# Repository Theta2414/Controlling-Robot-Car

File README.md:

# Controlling Robot Car

A wireless robot car control system implemented using STM32. The project uses an STM32-based transmitter and receiver architecture to control the movement of a robot car remotely. Motion commands are generated from user input and transmitted wirelessly to the robot, where the received commands are processed to control the motors.

The project focuses on embedded system development, wireless communication, sensor interfacing, PWM-based motor control, and real-time control using the STM32 microcontroller.

## 1. Project Overview

This project implements a wireless control system for a robot car using STM32 microcontrollers.

The system is divided into two main units:

- **Transmitter (Tx):** Reads user input and generates movement commands.
- **Receiver (Rx):** Receives the commands wirelessly and controls the robot car motors.

The transmitter and receiver communicate in real time, allowing the user to control the robot car's movement remotely.

The system is designed to support basic vehicle movements such as:

- Forward
- Backward
- Turn left
- Turn right
- Stop

PWM signals are used to control the motor speed, while the motor driver handles the required motor direction and power control.

## 2. Learning Objectives

- Practice embedded system development using STM32.
- Understand wireless communication between two embedded systems.
- Interface sensors and input devices with STM32.
- Understand PWM generation and motor speed control.
- Implement real-time control logic on a microcontroller.
- Apply UART/I2C/GPIO/TIMER peripherals where required by the system.
- Understand the separation between transmitter-side and receiver-side firmware.
- Improve debugging, hardware integration, and system-level development skills.
- Gain practical experience in developing a complete embedded system from input acquisition to actuator control.

## 3. System Architecture

The system consists of two main parts: a transmitter unit and a receiver unit.

### 3.1. Transmitter Unit

The transmitter is responsible for obtaining the user's control input and converting it into movement commands.

The general processing flow is:

```text
User Input / Motion Sensor
          ↓
    STM32 Transmitter
          ↓
   Control Processing
          ↓
  Wireless Transmission
```

The transmitter continuously reads the input data, processes the corresponding control information, and sends the resulting command to the receiver.

### 3.2. Receiver Unit

The receiver is installed on the robot car.

It receives the wireless control commands and converts them into motor control signals.

The general processing flow is:

```text
 Wireless Receiver
        ↓
  STM32 Receiver
        ↓
 Command Processing
        ↓
Direction + PWM Generation
        ↓
   Motor Driver
        ↓
    DC Motors
```

This architecture separates user interaction from the motor-control system and allows the robot to be controlled remotely.

## 4. Hardware Overview

The main hardware components used in the project include:

| Component                     | Purpose                    |
| ----------------------------- | -------------------------- |
| STM32F103C8T6                 | Main microcontroller       |
| MPU6050                       | Motion/tilt sensing        |
| Wireless communication module | Transmits control commands |
| Motor driver                  | Drives the DC motors       |
| DC motors                     | Provides robot movement    |
| Robot car chassis             | Mechanical platform        |
| Battery / Power supply        | Provides system power      |
| ST-Link                       | Programming and debugging  |

The STM32F103C8T6 is used as the main processing unit for both the transmitter and receiver sides.

The MPU6050 provides accelerometer and gyroscope measurements that can be processed to estimate the orientation of the transmitter.

## 5. Control Input and Motion Processing

The transmitter uses motion information to determine the desired movement of the robot car.

The MPU6050 provides accelerometer and gyroscope data. These measurements are processed to obtain stable Pitch and Roll angles.

A Kalman filter is used to combine information from the accelerometer and gyroscope and reduce measurement noise.

The general processing chain is:

```text
        MPU6050
           ↓
Accelerometer + Gyroscope
           ↓
    Sensor Processing
           ↓
     Kalman Filter
           ↓
    Pitch / Roll Angle
           ↓
    Movement Decision
           ↓
     Control Command
```

The resulting tilt angle is then mapped to a control value used by the system.

The operating angle is limited to:

```text
-45° ≤ θ ≤ +45°
```

and the corresponding control value is mapped to:

```text
-100 ≤ u ≤ +100
```

A dead zone is also applied around the neutral position to prevent small sensor fluctuations from unintentionally moving the robot.

For example:

```text
        Forward
           ↑
        Positive
           |
Left ←---  0° ---→ Right
           |
        Negative
           ↓
        Backward
```

The exact movement mapping depends on the control logic implemented in the transmitter firmware.

## 6. Wireless Communication

The transmitter and receiver communicate wirelessly.

The transmitter converts the processed user input into a control packet or command and sends it to the receiver.

The receiver continuously monitors the incoming data and determines the corresponding robot movement.

The communication flow can be represented as:

```text
             TRANSMITTER
                  │
          MPU6050 / User Input
                  │
                  ↓
           Control Processing
                  │
                  ↓
          Wireless Transmission
                  │
             ~~~~~~~~~~~
               Wireless
             Communication
             ~~~~~~~~~~~
                  │
                  ↓
          Wireless Reception
                  │
                  ↓
              RECEIVER
                  │
                  ↓
          Command Processing
                  │
                  ↓
          Motor Control Logic
                  │
                  ↓
            PWM + Direction
                  │
                  ↓
            Motor Driver
                  │
                  ↓
              Robot Car
```

The communication system is designed for real-time command transmission so that changes in the transmitter input are reflected by the robot car with low delay.

## 7. Motor Control

The receiver controls the robot's DC motors through a motor driver.

The direction of each motor is determined by the received movement command, while PWM is used to regulate motor speed.

The basic control structure is:

```text
 Received Command
        ↓
 Movement Decision
        ↓
 Direction Control
        +
  PWM Generation
        ↓
   Motor Driver
        ↓
    DC Motors
```

Different combinations of motor direction and PWM duty cycle are used to achieve forward, backward, left, right, and stop movements.

PWM provides a convenient way to control motor speed while keeping the STM32 in charge of the overall motion-control logic.

## 8. Software Architecture

The firmware is divided into transmitter-side and receiver-side software.

### 8.1. Transmitter Firmware

The transmitter firmware is responsible for:

- Initializing the STM32 peripherals.
- Reading MPU6050 data.
- Processing accelerometer and gyroscope measurements.
- Estimating Pitch and Roll angles.
- Applying the Kalman filter.
- Mapping the resulting angles to control values.
- Applying the control dead zone.
- Generating movement commands.
- Transmitting commands wirelessly.

The simplified software flow is:

```text
System Initialization
        ↓
   Read MPU6050
        ↓
Calculate Sensor Data
        ↓
   Kalman Filter
        ↓
Calculate Pitch / Roll
        ↓
  Angle Mapping
        ↓
    Dead Zone
        ↓
 Generate Command
        ↓
 Transmit Command
        ↓
     Repeat
```

The detailed transmitter flowchart is shown below:

### 8.2. Receiver Firmware

The receiver firmware is responsible for:

- Initializing the wireless communication interface.
- Receiving control commands.
- Decoding the received data.
- Determining the required movement.
- Generating motor direction signals.
- Generating PWM signals.
- Driving the motor driver.

The simplified software flow is:

```text
System Initialization
        ↓
 Wait for Command
        ↓
   Receive Data
        ↓
  Decode Command
        ↓
Determine Movement
        ↓
Set Motor Direction
        ↓
   Generate PWM
        ↓
   Drive Motors
        ↓
      Repeat
```

The detailed receiver flowchart is shown below:

## 9. Control Algorithm

The control algorithm converts the measured tilt angle into a motor-control command.

The angle is first limited to the valid operating range:

```text
-45° ≤ θ ≤ +45°
```

Then it is mapped to the control range:

```text
-100 ≤ u ≤ +100
```

A simplified linear mapping can be expressed as:

```text
u = (θ / 45) × 100
```

where:

- `θ` is the measured tilt angle.
- `u` is the resulting control value.

A dead zone is applied around the neutral position:

```text
-5° < θ < +5°
```

When the measured angle is inside this range, the control output is set to zero.

This prevents small sensor noise and minor hand movements from causing unwanted motor movement.

The overall control process is therefore:

```text
       Tilt Angle
           ↓
      Limit to ±45°
           ↓
       Map to ±100
           ↓
     Apply Dead Zone
           ↓
Generate Movement Command
           ↓
   Wireless Transmission
           ↓
      Motor Control
```

## 10. Timing and Real-Time Control

Real-time behavior is important because the robot needs to respond quickly to changes in user input.

The STM32 timer peripherals are used where periodic processing is required.

The control system continuously performs the following operations:

1. Acquire sensor data.
2. Process the sensor measurements.
3. Calculate the current control value.
4. Generate a movement command.
5. Transmit the command.
6. Receive and decode the command.
7. Update motor direction and PWM.

The control loop is designed to run continuously so that the robot can react to changes in the transmitter input.

Timing consistency is especially important for sensor processing and PWM-based motor control.

## 11. Safety and Stop Behavior

A stop condition is included in the control system to prevent the robot from continuing to move when there is no valid movement command.

When the control input is inside the defined neutral region, the motor command is set to zero.

This behavior can be represented as:

```text
          Input
            ↓
      Is command valid?
        /          \
      No            Yes
      ↓              ↓
    STOP        Process command
                     ↓
               Motor Control
```

A communication timeout or invalid-data handling mechanism can also be added to improve the safety of the system.

## 12. Pinout and Hardware Connections

The project uses STM32 GPIO, timer, I2C, and communication interfaces to connect the main components.

The major connections include:

| Interface          | Connected Device | Purpose                            |
| ------------------ | ---------------- | ---------------------------------- |
| I2C                | MPU6050          | Sensor communication               |
| GPIO               | Motor Driver     | Motor direction control            |
| TIMER/PWM          | Motor Driver     | Motor speed control                |
| Wireless Interface | Wireless Module  | Transmitter/receiver communication |
| ST-Link            | STM32            | Programming and debugging          |

## 13. Demo Video

A demonstration video showing the robot car and its wireless control system.

🎥 [Watch the Robot Car Demonstration Video](https://drive.google.com/file/d/1_pdBoHEz-EHRgsnchu68yCIKwLp6gopW/view?usp=sharing)

The demonstration shows the response of the robot car to different control inputs and verifies the communication between the transmitter and receiver.

## 14. Build and Flash

The project is developed for the STM32 microcontroller using an STM32-compatible embedded development environment.

Programming and debugging are performed using an ST-Link programmer/debugger.

General development flow:

```text
Write / Modify Firmware
          ↓
        Build
          ↓
    Generate Binary
          ↓
       ST-Link
          ↓
     Flash STM32
          ↓
     Test System
```

The transmitter and receiver firmware are built and programmed separately.

## 14.1. Finite State Machines

The transmitter firmware is organized around initialization, calibration, and active operation states:

The receiver firmware uses running and fail-safe states to handle normal operation and communication failure:

## 15. Development Tools

The project uses the following development tools and technologies:

- **MCU:** STM32F103C8T6
- **Programming Language:** C
- **IDE / Toolchain:** STM32 development environment
- **Programmer / Debugger:** ST-Link
- **Communication:** Wireless communication module
- **Sensor Interface:** I2C
- **Motor Control:** GPIO + PWM
- **Version Control:** Git / GitHub

## 16. Challenges and Design Considerations

Several practical challenges were considered during the development of the system.

### Sensor Noise

Raw accelerometer and gyroscope measurements contain noise and may produce unstable angle estimates.

The Kalman filter is therefore used to obtain a more stable estimation of the transmitter orientation.

### Control Sensitivity

Small changes in the measured angle can cause unwanted motor movement.

A dead zone around the neutral position is used to reduce this effect.

### Wireless Communication

The control system requires sufficiently responsive communication between the transmitter and receiver.

The transmitted data must also be interpreted correctly by the receiver to prevent incorrect movement.

### Motor Response

DC motors do not respond perfectly linearly to PWM changes. Factors such as friction, battery voltage, load, and motor characteristics can affect the actual movement of the robot.

Therefore, the PWM control range and movement thresholds may require practical adjustment during testing.

## 17. Limitations and Future Improvements

This project is primarily developed as an embedded systems learning project and therefore has several possible areas for improvement:

- Wireless communication reliability can be further improved.
- Sensor calibration can be enhanced for more consistent angle estimation.
- The control algorithm can be further tuned for smoother robot movement.
- Motor speed synchronization can be improved.
- A more robust communication protocol with packet validation can be implemented.
- Communication timeout and automatic emergency-stop mechanisms can be added.
- Battery voltage monitoring can be added.
- Additional sensors can be integrated for obstacle detection.
- The software architecture can be further modularized for easier maintenance.
- Closed-loop motor control using wheel encoders can be considered for more accurate movement.

Possible future extensions include:

```text
Current System
     │
     ├── Wireless Control
     ├── MPU6050
     ├── PWM Motor Control
     │
     ↓
Future Improvements
     │
     ├── Encoder Feedback
     ├── Closed-loop Control
     ├── Obstacle Detection
     ├── Battery Monitoring
     ├── Improved Communication Protocol
     └── More Advanced Control Algorithms
```

## 18. Conclusion

This project demonstrates the development of a wireless robot car control system using STM32.

The system combines sensor acquisition, motion estimation, wireless communication, command processing, and PWM-based motor control into a complete embedded application.

Through this project, the system provides practical experience in integrating multiple embedded peripherals and developing a real-time control system from the transmitter input to the physical movement of the robot.

## 19. Team Members

### Team Information

**Team:** PỎSCHE WITH NO BRAKES  
**Mentor:** Võ Quang Vinh

### Our Team

👑 **Team Leader**  
- Mạch Viễn An

👥 **Team Members**  
- Phạm Đỗ Hồng Phúc
- Nguyễn Phúc Khải
- Nguyễn Công Tú

The project was developed as a collaborative team project under the guidance of our mentor.

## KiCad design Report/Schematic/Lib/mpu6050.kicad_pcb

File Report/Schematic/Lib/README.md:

# MPU6050_Kicad
MPU6050模块Kicad PCB工程文件

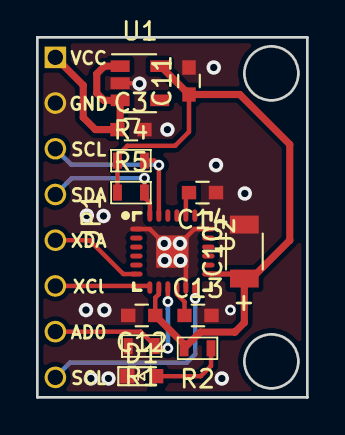
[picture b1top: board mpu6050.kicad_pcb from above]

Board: 2 copper layers, 15.0 x 20.0 mm, 14 parts (0 on the bottom side), 12 nets.

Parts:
C3: 4.7uF; C_0603
C10: 10uF; C_1206
C11, C12, C13: 0.1uF; C_0603
C14: 2.2nF; C_0603
D1: LED; LED_0603
JP1: JACK8; DIP-1.5Hole-2.54mm-Pitch-8P
R1, R2, R4, R5: 4.7K; R_0603
U1: SPX3819M5-L-3-3; SOT-23-5
U2: MPU-6050; QFN-24_4X4X05P

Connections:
+3V3: C10.1, C11.1, C12.1, R2.2, R4.1, R5.1, U1.5, U2.8, U2.13
+5V: C3.1, JP1.1, U1.1, U1.3
/AD0: JP1.7, R1.1, U2.9
/INT: JP1.8, U2.12
/SCL: JP1.3, R4.2, U2.23
/SDA: JP1.4, R5.2, U2.24
/XCL: JP1.6, U2.7
/XDA: JP1.5, U2.6
GND: C3.2, C10.2, C11.2, C12.2, C13.2, C14.1, D1.1, JP1.2, R1.2, U1.2, U2.0, U2.1, U2.11, U2.18
unnamed: C13.1, U2.10
unnamed: C14.2, U2.20
unnamed: D1.2, R2.1
